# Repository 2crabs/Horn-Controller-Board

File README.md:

# Horn Controller v0.1

Controller board for signal horns on a sailing race course and designed for reliability and easy integration. The board includes features such as ...

* __Current-sensing__: Current sensor at output of relays for making sure that motor is connected and running
* __Multiple Relays__: Two relays combined with logic to account for one of the relays failing
* __Large Display__: Large seven segment displays making it easy to see the countdown from a distance
* __Wago Connectors__: Easy to conect the power and motor wires, without the need to crimp on any connectors
* __CAN Bus__: Reliable and flexible communication with a remote control

## Resources
[Schematic](Schematic.pdf)

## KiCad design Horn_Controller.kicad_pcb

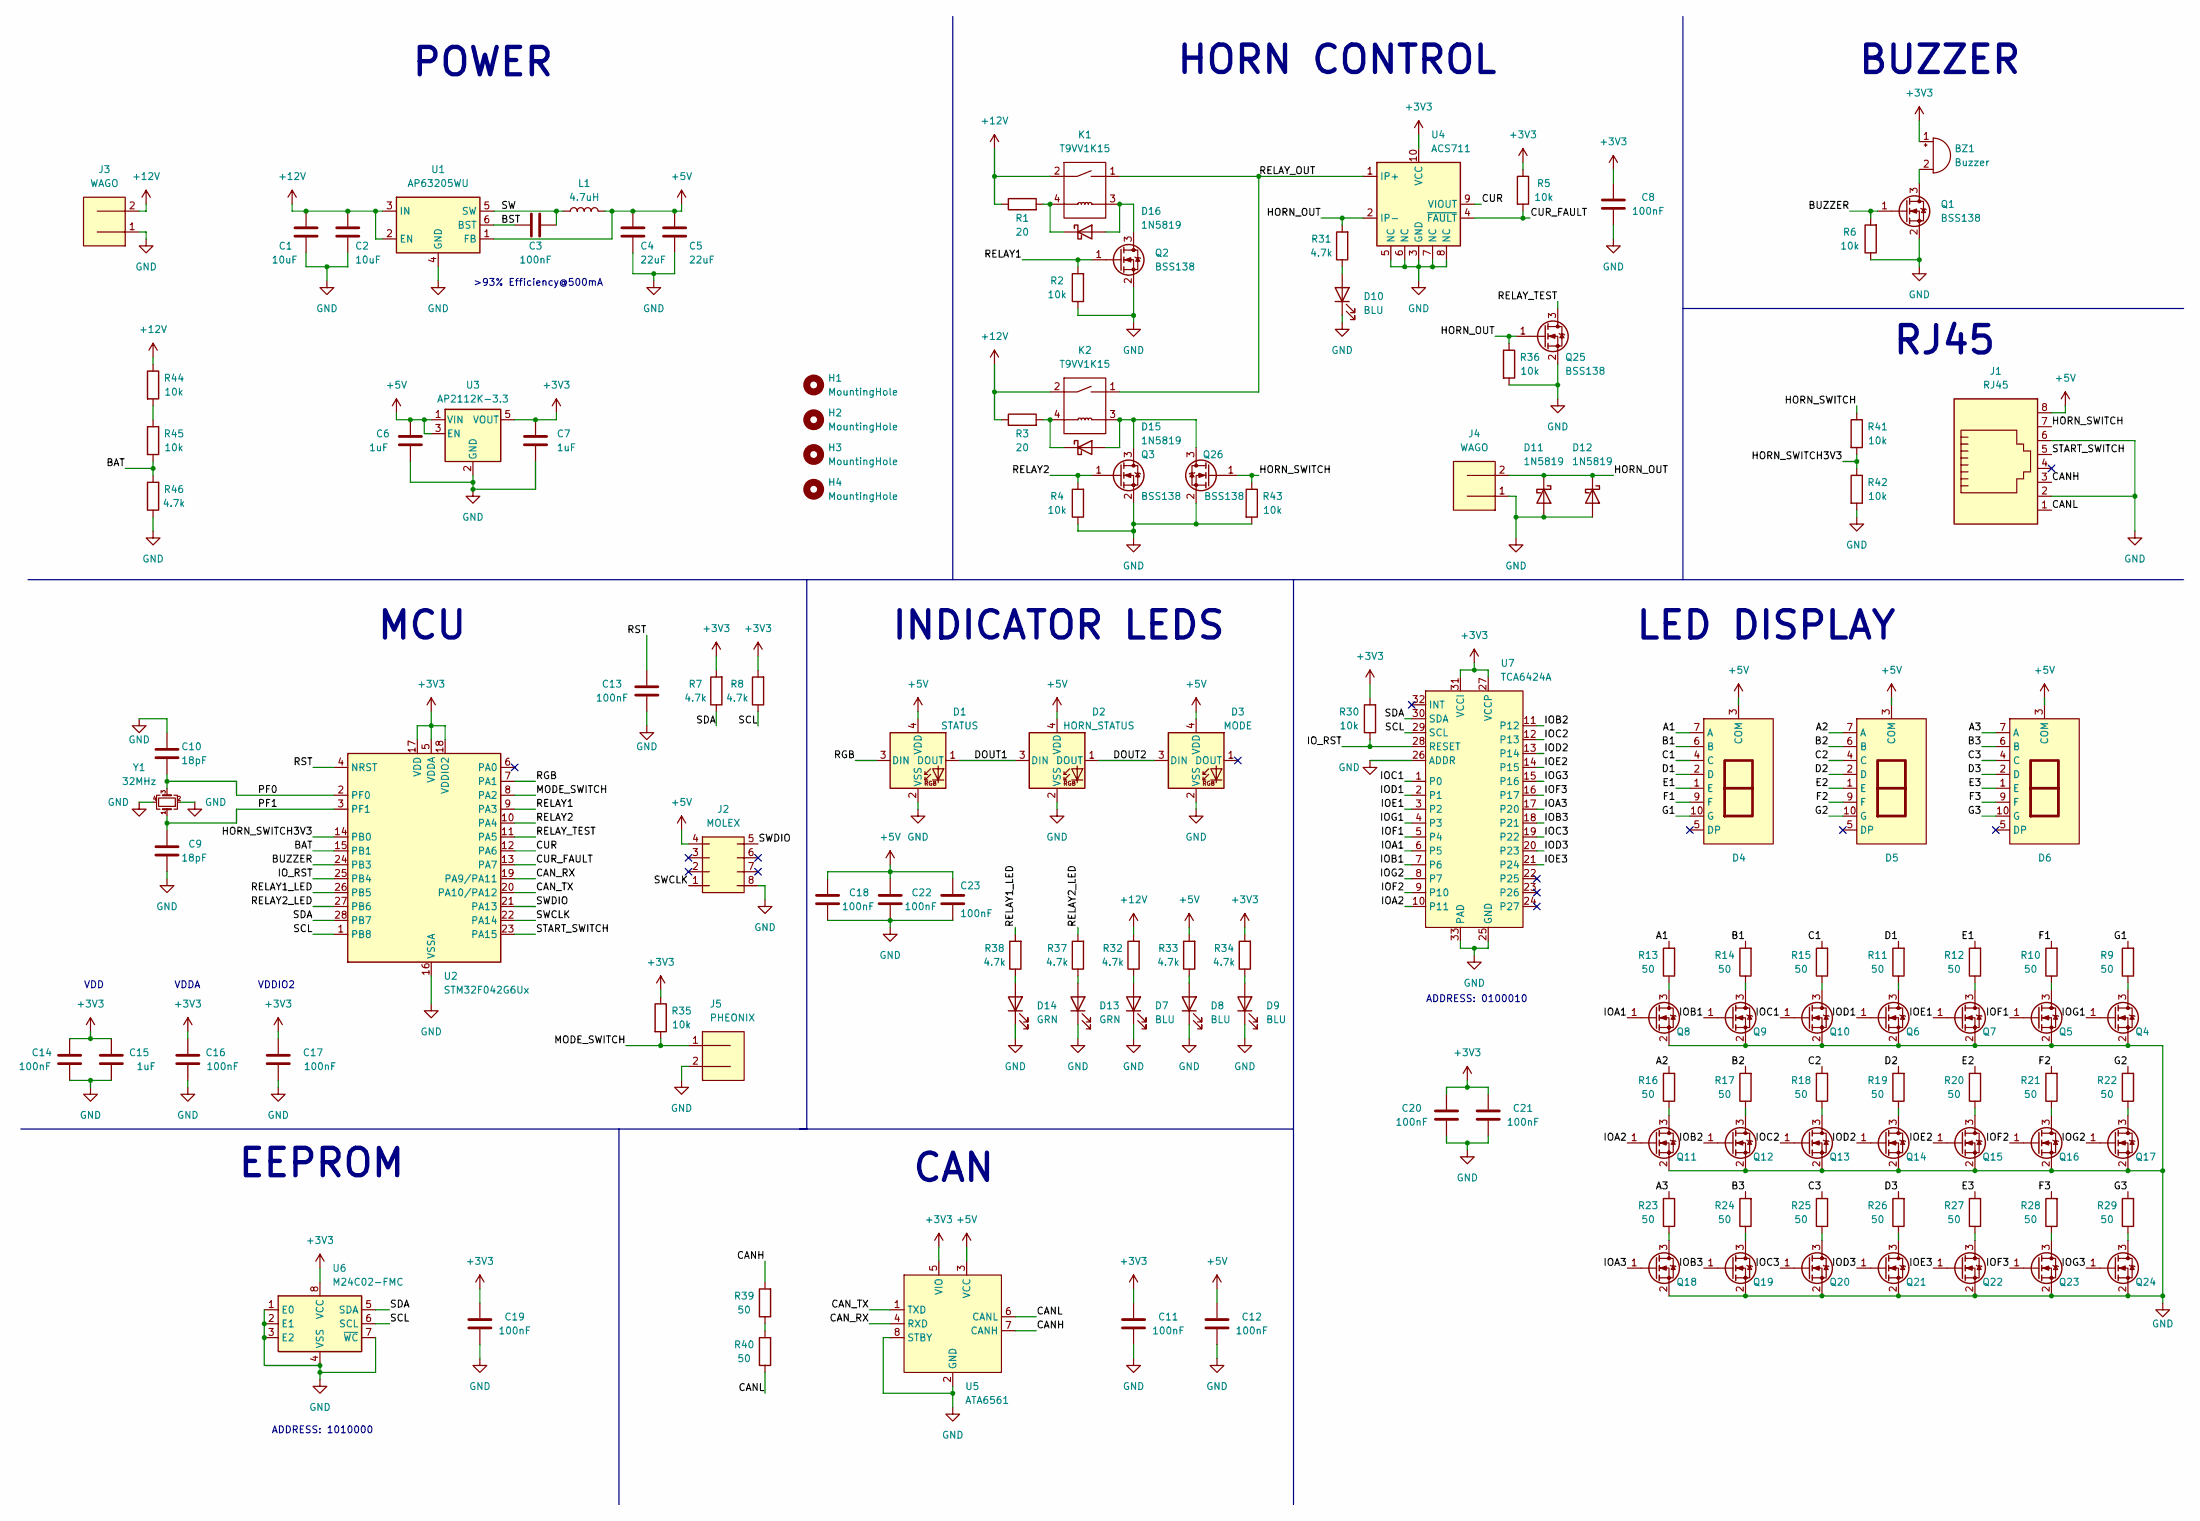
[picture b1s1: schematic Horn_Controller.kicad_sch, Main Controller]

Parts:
BZ1: Buzzer; CUI_CMI-9705-0380-SMT-TR
C1, C2: 10uF; C_0805_2012Metric
C3, C8, C11, C12, C13, C14, C16, C17, C18, C19, C20, C21, C22, C23: 100nF; C_0402_1005Metric
C4, C5: 22uF; C_0805_2012Metric
C6, C7, C15: 1uF; C_0603_1608Metric
C9, C10: 18pF; C_0603_1608Metric
D1: STATUS; WS2812B-2020
D2: HORN_STATUS; WS2812B-2020
D3: MODE; WS2812B-2020
D4, D5, D6: ARKLED-1IN
D7, D8, D9, D10: BLU; LED_0603_1608Metric
D11, D12, D15, D16: 1N5819; D_SOD-123
D13, D14: GRN; LED_0603_1608Metric
H1, H2, H3, H4: MountingHole; MountingHole_3.2mm_M3_Pad
J1: RJ45; rj45
J2: MOLEX; 5050040812-MOLEX
J3, J4: WAGO; 2604-WAGO
J5: PHEONIX; 1751765-Pheonix
K1, K2: T9VV1K15; T9V-Relay
L1: 4.7uH; L_1008_2520Metric
Q1, Q2, Q3, Q4, Q5, Q6, Q7, Q8, Q9, Q10, Q11, Q12, Q13, Q14, Q15, Q16, Q17, Q18, Q19, Q20, Q21, Q22, Q23, Q24, Q25, Q26: BSS138; SOT-23
R1, R3: 20; R_2512_6332Metric
R2, R4, R5, R6, R30, R35, R36, R41, R42, R43, R44, R45: 10k; R_0603_1608Metric
R7, R8, R31, R32, R33, R34, R37, R38, R46: 4.7k; R_0603_1608Metric
R9, R10, R11, R12, R13, R14, R15, R16, R17, R18, R19, R20, R21, R22, R23, R24, R25, R26, R27, R28, R29, R39, R40: 50; R_0603_1608Metric
U1: AP63205WU; TSOT-23-6
U2: STM32F042G6Ux; QFN-28_4x4mm_P0.5mm
U3: AP2112K-3.3; SOT-23-5
U4: ACS711; Allegro_QFN-12-10-1EP_3x3mm_P0.5mm
U5: ATA6561; DFN-8-1EP_3x3mm_P0.65mm_EP1.7x2.05mm
U6: M24C02-FMC; 8-UFDFPN
U7: TCA6424A; VQFN-32-1EP_5x5mm_P0.5mm_EP3.15x3.15mm_ThermalVias
Y1: 32MHz; Crystal_SMD_3225-4Pin_3.2x2.5mm

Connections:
+3V3: BZ1.1 (+), C7.1, C8.1, C11.1, C14.1, C15.1, C16.1, C17.1, C19.1, C20.1, C21.1, R5.1, R7.2, R8.2, R30.2, R34.2, R35.1, U2.5 (VDDA), U2.17 (VDD), U2.18 (VDDIO2), U3.5 (VOUT), U4.10 (VCC), U5.5 (VIO), U6.8 (VCC), U7.27 (VCCP), U7.31 (VCCI)
+5V: C4.1, C5.1, C6.1, C12.1, C18.1, C22.1, C23.1, D1.4 (VDD), D2.4 (VDD), D3.4 (VDD), D4.3 (COM), D5.3 (COM), D6.3 (COM), J1.8, J2.4, L1.2, R33.2, U1.1 (FB), U3.1 (VIN), U3.3 (EN), U5.3 (VCC)
+12V: C1.1, C2.1, J3.2, K1.2, K2.2, R1.1, R3.1, R32.2, R44.1, U1.2 (EN), U1.3 (IN)
/A1: D4.7 (A), R13.2
/A2: D5.7 (A), R16.2
/A3: D6.7 (A), R23.2
/B1: D4.6 (B), R14.2
/B2: D5.6 (B), R17.2
/B3: D6.6 (B), R24.2
/BAT: R45.2, R46.2, U2.15 (PB1)
/BST: C3.2, U1.6 (BST)
/BUZZER: Q1.1 (G), R6.2, U2.24 (PB3)
/C1: D4.4 (C), R15.2
/C2: D5.4 (C), R18.2
/C3: D6.4 (C), R25.2
/CANH: J1.3, R39.2, U5.7 (CANH)
/CANL: J1.1, R40.1, U5.6 (CANL)
/CAN_RX: U2.19 (PA9/PA11), U5.4 (RXD)
/CAN_TX: U2.20 (PA10/PA12), U5.1 (TXD)
/CUR: U2.12 (PA6), U4.9 (VIOUT)
/CUR_FAULT: R5.2, U2.13 (PA7), U4.4 (~FAULT)
/D1: D4.2 (D), R11.2
/D2: D5.2 (D), R19.2
/D3: D6.2 (D), R26.2
/DOUT1: D1.1 (DOUT), D2.3 (DIN)
/DOUT2: D2.1 (DOUT), D3.3 (DIN)
/E1: D4.1 (E), R12.2
/E2: D5.1 (E), R20.2
/E3: D6.1 (E), R27.2
/F1: D4.9 (F), R10.2
/F2: D5.9 (F), R21.2
/F3: D6.9 (F), R28.2
/G1: D4.10 (G), R9.2
/G2: D5.10 (G), R22.2
/G3: D6.10 (G), R29.2
/HORN_OUT: D11.1 (K), D12.1 (K), J4.2, Q25.1 (G), R31.2, R36.1, U4.2 (IP-)
/HORN_SWITCH: J1.7, Q26.1 (G), R41.1, R43.1
/HORN_SWITCH3V3: R41.2, R42.1, U2.14 (PB0)
/IOA1: Q8.1 (G), U7.6 (P5)
/IOA2: Q11.1 (G), U7.10 (P11)
/IOA3: Q18.1 (G), U7.17 (P20)
/IOB1: Q9.1 (G), U7.7 (P6)
/IOB2: Q12.1 (G), U7.11 (P12)
/IOB3: Q19.1 (G), U7.18 (P21)
/IOC1: Q10.1 (G), U7.1 (P0)
/IOC2: Q13.1 (G), U7.12 (P13)
/IOC3: Q20.1 (G), U7.19 (P22)
/IOD1: Q6.1 (G), U7.2 (P1)
/IOD2: Q14.1 (G), U7.13 (P14)
/IOD3: Q21.1 (G), U7.20 (P23)
/IOE1: Q7.1 (G), U7.3 (P2)
/IOE2: Q15.1 (G), U7.14 (P15)
/IOE3: Q22.1 (G), U7.21 (P24)
/IOF1: Q5.1 (G), U7.5 (P4)
/IOF2: Q16.1 (G), U7.9 (P10)
/IOF3: Q23.1 (G), U7.16 (P17)
/IOG1: Q4.1 (G), U7.4 (P3)
/IOG2: Q17.1 (G), U7.8 (P7)
/IOG3: Q24.1 (G), U7.15 (P16)
/IO_RST: R30.1, U2.25 (PB4), U7.28 (RESET)
/MODE_SWITCH: J5.1, R35.2, U2.8 (PA2)
/PF0: C10.2, U2.2 (PF0), Y1.3
/PF1: C9.1, U2.3 (PF1), Y1.1
/RELAY1: Q2.1 (G), R2.2, U2.9 (PA3)
/RELAY1_LED: R38.2, U2.26 (PB5)
/RELAY2: Q3.1 (G), R4.2, U2.10 (PA4)
/RELAY2_LED: R37.2, U2.27 (PB6)
/RELAY_OUT: K1.1, K2.1, U4.1 (IP+)
/RELAY_TEST: Q25.3 (D), U2.11 (PA5)
/RGB: D1.3 (DIN), U2.7 (PA1)
/RST: C13.1, U2.4 (NRST)
/SCL: R8.1, U2.1 (PB8), U6.6 (SCL), U7.29 (SCL)
/SDA: R7.1, U2.28 (PB7), U6.5 (SDA), U7.30 (SDA)
/START_SWITCH: J1.5, U2.23 (PA15)
/SW: C3.1, L1.1, U1.5 (SW)
/SWCLK: J2.1, U2.22 (PA14)
/SWDIO: J2.5, U2.21 (PA13)
GND: C1.2, C2.2, C4.2, C5.2, C6.2, C7.2, C8.2, C9.2, C10.1, C11.2, C12.2, C13.2, C14.2, C15.2, C16.2, C17.2, C18.2, C19.2, C20.2, C21.2, C22.2, C23.2, D1.2 (VSS), D2.2 (VSS), D3.2 (VSS), D7.1 (K), D8.1 (K), D9.1 (K), D10.1 (K), D11.2 (A), D12.2 (A), D13.1 (K), D14.1 (K), J1.2, J1.6, J2.8, J3.1, J4.1, J5.2, Q1.2 (S), Q2.2 (S), Q3.2 (S), Q4.2 (S), Q5.2 (S), Q6.2 (S), Q7.2 (S), Q8.2 (S), Q9.2 (S), Q10.2 (S), Q11.2 (S), Q12.2 (S), Q13.2 (S), Q14.2 (S), Q15.2 (S), Q16.2 (S), Q17.2 (S), Q18.2 (S), Q19.2 (S), Q20.2 (S), Q21.2 (S), Q22.2 (S), Q23.2 (S), Q24.2 (S), Q25.2 (S), Q26.2 (S), R2.1, R4.1, R6.1, R36.2, R42.2, R43.2, R46.1, U1.4 (GND), U2.16 (VSSA), U3.2 (GND), U4.3 (GND), U4.5 (NC), U4.6 (NC), U4.7 (NC), U4.8 (NC), U5.2 (GND), U5.8 (STBY), U5.9, U6.1 (E0), U6.2 (E1), U6.3 (E2), U6.4 (VSS), U6.7 (~WC), U7.25 (GND), U7.26 (ADDR), U7.33 (PAD), Y1.2, Y1.4
unnamed: BZ1.2 (-), Q1.3 (D)
unnamed: D7.2 (A), R32.1
unnamed: D8.2 (A), R33.1
unnamed: D9.2 (A), R34.1
unnamed: D10.2 (A), R31.1
unnamed: D13.2 (A), R37.1
unnamed: D14.2 (A), R38.1
unnamed: D15.2 (A), K2.3, Q3.3 (D), Q26.3 (D)
unnamed: D15.1 (K), K2.4, R3.2
unnamed: D16.2 (A), K1.3, Q2.3 (D)
unnamed: D16.1 (K), K1.4, R1.2
unnamed: Q4.3 (D), R9.1
unnamed: Q5.3 (D), R10.1
unnamed: Q6.3 (D), R11.1
unnamed: Q7.3 (D), R12.1
unnamed: Q8.3 (D), R13.1
unnamed: Q9.3 (D), R14.1
unnamed: Q10.3 (D), R15.1
unnamed: Q11.3 (D), R16.1
unnamed: Q12.3 (D), R17.1
unnamed: Q13.3 (D), R18.1
unnamed: Q14.3 (D), R19.1
unnamed: Q15.3 (D), R20.1
unnamed: Q16.3 (D), R21.1
unnamed: Q17.3 (D), R22.1
unnamed: Q18.3 (D), R23.1
unnamed: Q19.3 (D), R24.1
unnamed: Q20.3 (D), R25.1
unnamed: Q21.3 (D), R26.1
unnamed: Q22.3 (D), R27.1
unnamed: Q23.3 (D), R28.1
unnamed: Q24.3 (D), R29.1
unnamed: R39.1, R40.2
unnamed: R44.2, R45.1

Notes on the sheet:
HORN CONTROL
EEPROM
INDICATOR LEDS
ADDRESS: 0100010
CAN
VDD
LED DISPLAY
ADDRESS: 1010000
VDDIO2
>93% Efficiency@500mA
BUZZER
RJ45
POWER
VDDA
MCU

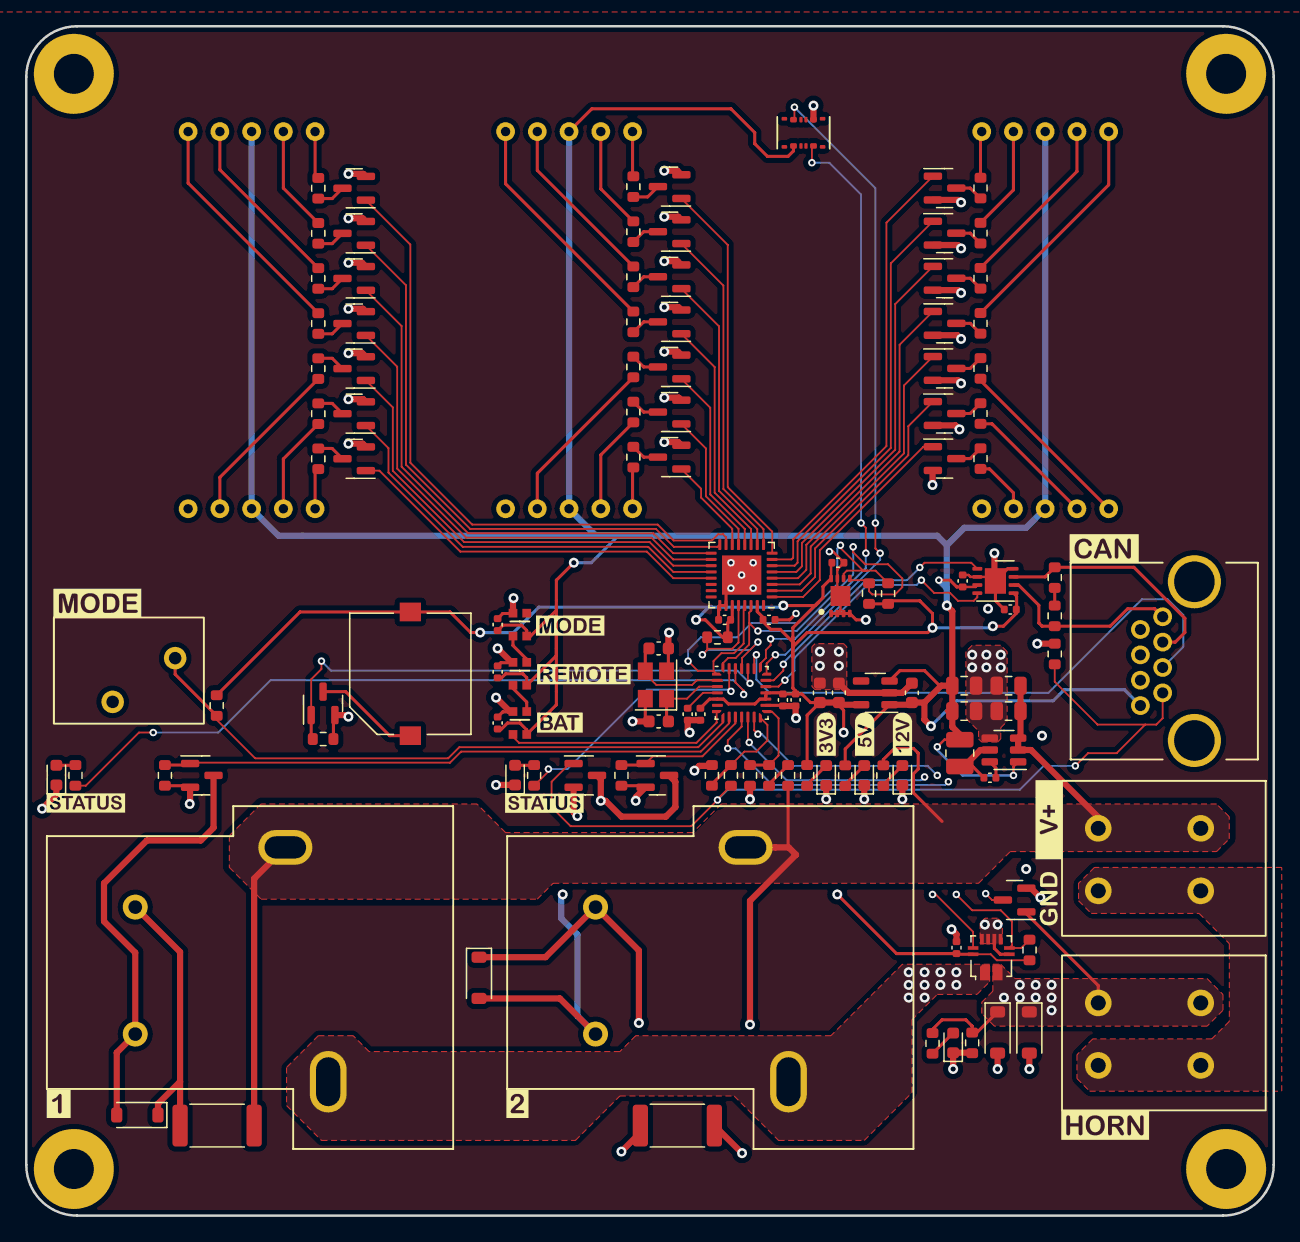
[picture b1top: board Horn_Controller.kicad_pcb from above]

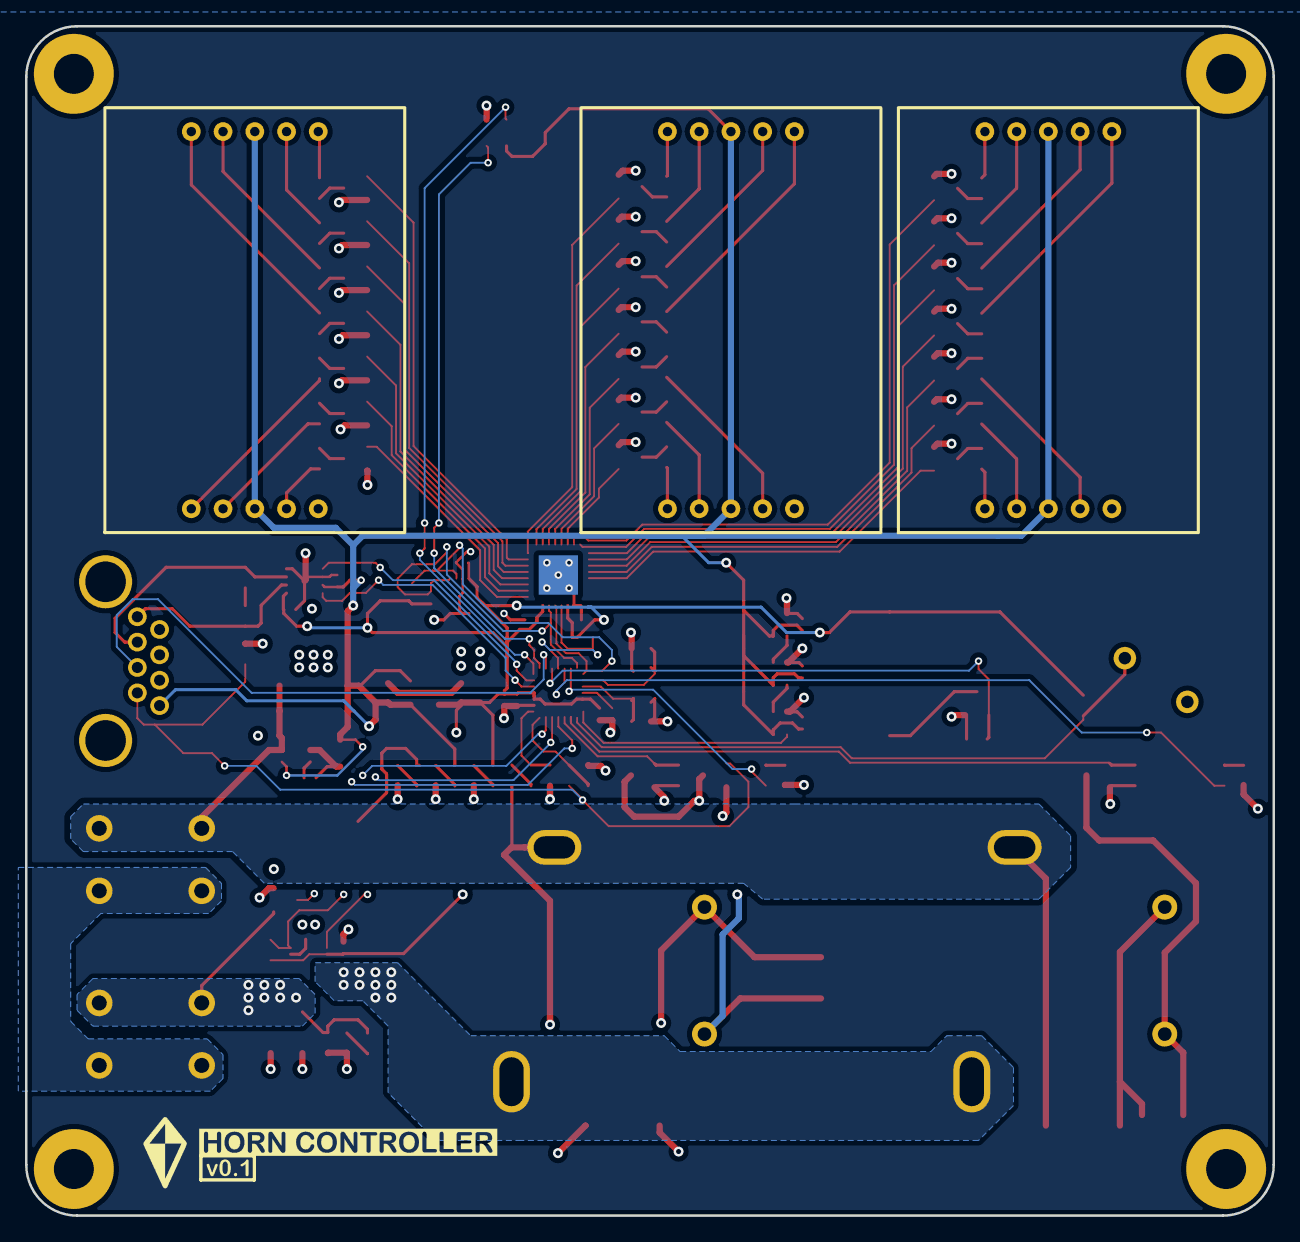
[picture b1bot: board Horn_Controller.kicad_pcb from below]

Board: 4 copper layers, 99.8 x 95.2 mm, 132 parts (3 on the bottom side), 112 nets.

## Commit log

2024-12-07 Project files
2025-10-15 Added missing I2C trace
2025-10-15 Schematic readability changes
2025-10-15 Added Schematic PDF
